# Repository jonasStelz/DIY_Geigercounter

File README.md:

# ESP32-S3 Geiger Counter PCB

A custom-designed **battery-powered** Geiger counter board created in **KiCad**, featuring an **ESP32-S3-WROOM-1** module, an LCD display, and a high-voltage section for driving a Geiger–Müller tube.

This project combines radiation detection with IoT capabilities, allowing live data display and wireless transmission without being tethered to a power source.

---

## Features

- **ESP32-S3-WROOM-1** microcontroller for high performance and Wi-Fi/Bluetooth connectivity  
- **LCD display** for real-time radiation readings and system status  
- Integrated **high-voltage generator** for Geiger–Müller tube operation  
- **USB-C** connector for charging and programming  
- **Battery-powered** for portable use (Li-ion/LiPo support)  
- Compact PCB layout for handheld or embedded use  
- Designed entirely in **KiCad**

---

## Hardware Overview

The PCB integrates both the high-voltage section (for the tube) and the low-voltage digital section (ESP32 + display + battery management) on the same board.  
Special care has been taken to separate HV signals from sensitive logic lines.

---

## Feedback & Contributions

This is my first PCB design combining high-voltage circuitry with an ESP32-S3 microcontroller.  
I welcome **design reviews, suggestions, and improvements** — especially regarding:  
- HV layout and safety clearances  
- EMC and noise reduction  
- Power supply stability (especially with battery use)  
- General PCB best practices  

If you spot an issue or have an idea, please open an **Issue** or submit a **Pull Request**.

---

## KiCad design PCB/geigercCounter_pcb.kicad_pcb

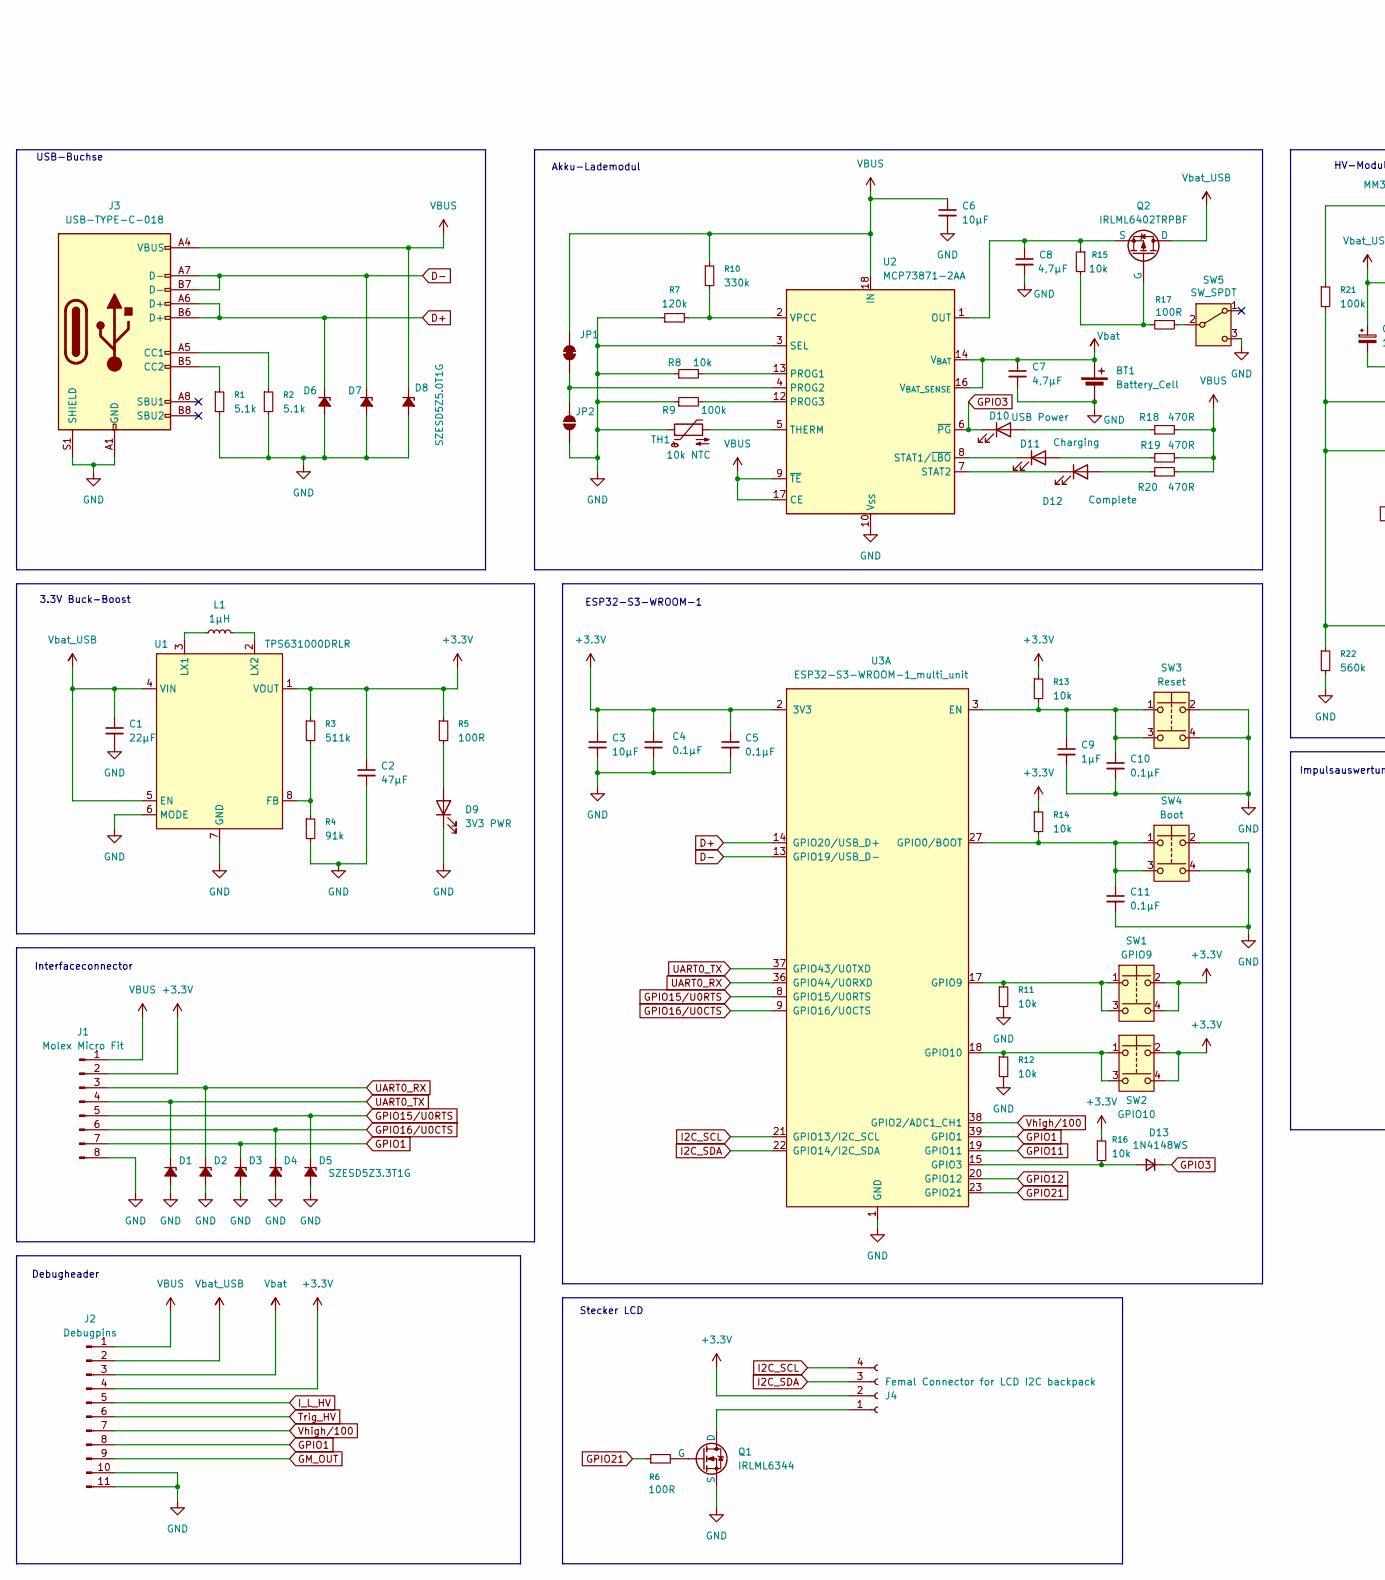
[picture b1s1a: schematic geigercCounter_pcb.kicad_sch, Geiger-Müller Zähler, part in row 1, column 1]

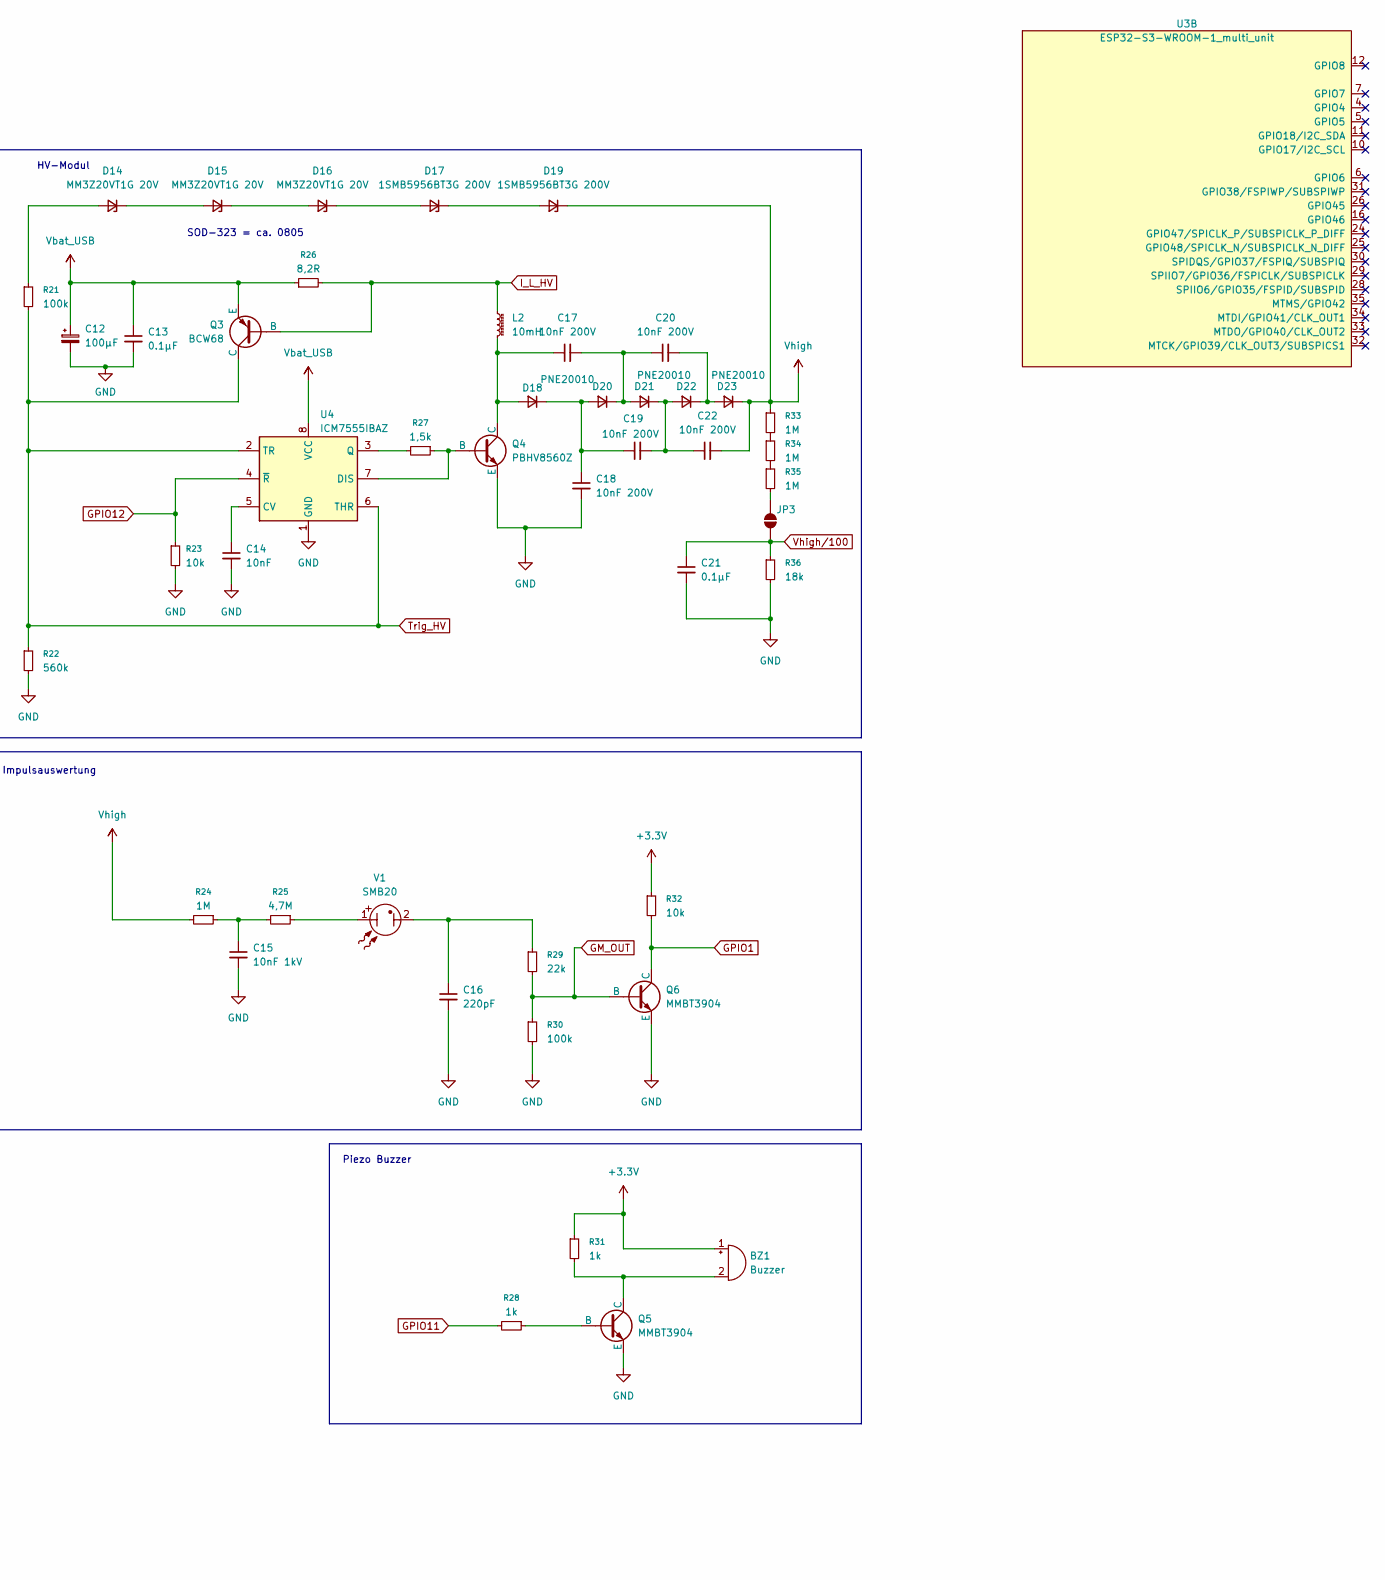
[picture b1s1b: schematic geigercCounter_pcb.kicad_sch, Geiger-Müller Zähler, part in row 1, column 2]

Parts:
BT1: Battery_Cell; JST_PH_B2B-PH-SM4-TB_1x02-1MP_P2.00mm_Vertical
BZ1: Buzzer; CMI-9705-0380
C1: 22µF; C_0805_2012Metric_Pad1.18x1.45mm_HandSolder
C2: 47µF; C_0805_2012Metric_Pad1.18x1.45mm_HandSolder
C3, C6: 10µF; C_0805_2012Metric_Pad1.18x1.45mm_HandSolder
C4, C5, C10, C11, C13, C21: 0.1µF; C_0805_2012Metric_Pad1.18x1.45mm_HandSolder
C7, C8: 4,7µF; C_0805_2012Metric_Pad1.18x1.45mm_HandSolder
C9: 1µF; C_0805_2012Metric_Pad1.18x1.45mm_HandSolder
C12: 100µF; CP_Elec_6.3x5.9
C14: 10nF; C_0805_2012Metric_Pad1.18x1.45mm_HandSolder
C15: 10nF 1kV; C_1206_3216Metric_Pad1.33x1.80mm_HandSolder
C16: 220pF; C_0805_2012Metric_Pad1.18x1.45mm_HandSolder
C17, C18, C19, C20, C22: 10nF 200V; C_0805_2012Metric_Pad1.18x1.45mm_HandSolder
D1, D2, D3, D4, D5: SZESD5Z3.3T1G; D_SOD-523
D6, D7, D8: SZESD5Z5.0T1G; D_SOD-523
D9: 3V3 PWR; LED_0805_2012Metric_Pad1.15x1.40mm_HandSolder
D10: USB Power; LED_0805_2012Metric_Pad1.15x1.40mm_HandSolder
D11: Charging; LED_0805_2012Metric_Pad1.15x1.40mm_HandSolder
D12: Complete; LED_0805_2012Metric_Pad1.15x1.40mm_HandSolder
D13: 1N4148WS; D_SOD-323_HandSoldering
D14, D15, D16: MM3Z20VT1G 20V; D_SOD-323_HandSoldering
D17, D19: 1SMB5956BT3G 200V; D_SMB_Handsoldering
D18, D20, D21, D22, D23: PNE20010; Nexperia_CFP3_SOD-123W
J1: Molex Micro Fit; Molex_Micro-Fit_3.0_43045-0810_2x04-1MP_P3.00mm_Horizontal
J2: Debugpins; PinHeader_1x11_P2.54mm_Vertical
J3: USB-TYPE-C-018; USB_C_Receptacle_GCT_USB4105-xx-A_16P_TopMnt_Horizontal
J4: Femal Connector for LCD I2C backpack; PinHeader_1x04_P2.54mm_Horizontal
JP1: SolderJumper_2_Bridged; SolderJumper-2_P1.3mm_Open_RoundedPad1.0x1.5mm
JP2, JP3: SolderJumper_2_Open; SolderJumper-2_P1.3mm_Open_RoundedPad1.0x1.5mm
L1: 1µH; Murata_DFE252012P
L2: 10mH; Inductor_wuerth_7447709222
Q1: IRLML6344; SOT-23-3
Q2: IRLML6402TRPBF; SOT-23-3
Q3: BCW68; SOT-23-3
Q4: PBHV8560Z; SOT-223-3_TabPin2
Q5, Q6: MMBT3904; SOT-23-3
R1, R2: 5.1k; R_0805_2012Metric_Pad1.20x1.40mm_HandSolder
R3: 511k; R_0805_2012Metric_Pad1.20x1.40mm_HandSolder
R4: 91k; R_0805_2012Metric_Pad1.20x1.40mm_HandSolder
R5, R6, R17: 100R; R_0805_2012Metric_Pad1.20x1.40mm_HandSolder
R7: 120k; R_0805_2012Metric_Pad1.20x1.40mm_HandSolder
R8, R11, R12, R13, R14, R15, R16, R23, R32: 10k; R_0805_2012Metric_Pad1.20x1.40mm_HandSolder
R9, R21, R30: 100k; R_0805_2012Metric_Pad1.20x1.40mm_HandSolder
R10: 330k; R_0805_2012Metric_Pad1.20x1.40mm_HandSolder
R18, R19, R20: 470R; R_0805_2012Metric_Pad1.20x1.40mm_HandSolder
R22: 560k; R_0805_2012Metric_Pad1.20x1.40mm_HandSolder
R24, R33, R34, R35: 1M; R_0805_2012Metric_Pad1.20x1.40mm_HandSolder
R25: 4,7M; R_0805_2012Metric_Pad1.20x1.40mm_HandSolder
R26: 8,2R; R_0805_2012Metric_Pad1.20x1.40mm_HandSolder
R27: 1,5k; R_0805_2012Metric_Pad1.20x1.40mm_HandSolder
R28, R31: 1k; R_0805_2012Metric_Pad1.20x1.40mm_HandSolder
R29: 22k; R_0805_2012Metric_Pad1.20x1.40mm_HandSolder
R36: 18k; R_0805_2012Metric_Pad1.20x1.40mm_HandSolder
SW1: GPIO9; SW_Push_1P1T_NO_E-Switch_TL3301NxxxxxG
SW2: GPIO10; SW_Push_1P1T_NO_E-Switch_TL3301NxxxxxG
SW3: Reset; SW_Push_1P1T_NO_E-Switch_TL3301NxxxxxG
SW4: Boot; SW_Push_1P1T_NO_E-Switch_TL3301NxxxxxG
SW5: SW_SPDT; SW_SPDT_PCM12
TH1: 10k NTC; R_0805_2012Metric_Pad1.20x1.40mm_HandSolder
U1: TPS631000DRLR; SOT-583-8
U2: MCP73871-2AA; QFN-20-1EP_4x4mm_P0.5mm_EP2.5x2.5mm
U3: ESP32-S3-WROOM-1_multi_unit; ESP32-S3-WROOM-1
U4: ICM7555IBAZ; SOIC-8_3.9x4.9mm_P1.27mm
V1: SMB20; SBM-20

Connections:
+3.3V: BZ1.1 (+), C2.1, C3.1, C4.1, C5.1, J1.2, J2.4, J4.2, R3.1, R5.1, R13.1, R14.1, R16.1, R31.1, R32.1, SW1.2, SW1.4 (1), SW2.2, SW2.4 (2), U1.1 (VOUT), U3.2 (3V3)
D+: D6.1 (K), J3.A6 (D+), J3.B6 (D+), U3.14 (GPIO20/USB_D+)
D-: D7.1 (K), J3.A7 (D-), J3.B7 (D-), U3.13 (GPIO19/USB_D-)
GM_OUT: J2.9, Q6.1 (B), R29.2, R30.1
GND: BT1.2 (-), C1.2, C2.2, C3.2, C4.2, C5.2, C6.2, C7.2, C8.2, C9.2, C10.2, C11.2, C12.2, C13.2, C14.2, C15.2, C16.2, C18.2, C21.2, D1.2 (A), D2.2 (A), D3.2 (A), D4.2 (A), D5.2 (A), D6.2 (A), D7.2 (A), D8.2 (A), D9.1 (K), J1.8, J1.MP, J2.10, J2.11, J3.A1 (GND), J3.A12 (GND), J3.B1 (GND), J3.B12 (GND), J3.S1 (SHIELD), JP2.1 (A), Q1.2 (S), Q4.3 (E), Q5.2 (E), Q6.2 (E), R1.2, R2.2, R4.2, R7.1, R8.1, R9.1, R11.2, R12.2, R22.2, R23.2, R30.2, R36.2, SW3.2, SW3.4 (2), SW4.2, SW4.4 (1), SW5.3 (C), TH1.1, U1.6 (MODE), U1.7 (GND), U2.3 (SEL), U2.10 (V_{SS}), U2.11 (V_{SS}), U2.21 (V_{SS}), U3.1 (GND), U3.40 (GND), U3.41 (GND), U4.1 (GND)
GPIO1: D3.1 (K), J1.7, J2.8, Q6.3 (C), R32.2, U3.39 (GPIO1)
GPIO3: D10.1 (K), D13.1 (K), U2.6 (~PG)
GPIO11: R28.2, U3.19 (GPIO11)
GPIO12: R23.1, U3.20 (GPIO12), U4.4 (~R)
GPIO15/U0RTS: D5.1 (K), J1.5, U3.8 (GPIO15/U0RTS)
GPIO16/U0CTS: D4.1 (K), J1.6, U3.9 (GPIO16/U0CTS)
GPIO21: R6.1, U3.23 (GPIO21)
I2C_SCL: J4.4, U3.21 (GPIO13/I2C_SCL)
I2C_SDA: J4.3, U3.22 (GPIO14/I2C_SDA)
I_L_HV: J2.5, L2.1, Q3.1 (B), R26.2
unnamed: BZ1.2 (-), Q5.3 (C), R31.2
unnamed: C15.1, R24.1, R25.2
unnamed: C16.1, R29.1, V1.2
unnamed: D9.2 (A), R5.2
unnamed: D10.2 (A), R18.1
unnamed: D11.2 (A), R19.2
unnamed: D11.1 (K), U2.8 (STAT1/~LBO)
unnamed: D12.2 (A), R20.1
unnamed: D12.1 (K), U2.7 (STAT2)
unnamed: D13.2 (A), R16.2, U3.15 (GPIO3)
unnamed: D14.2 (A), R21.1
unnamed: D14.1 (K), D15.2 (A)
unnamed: D15.1 (K), D16.2 (A)
unnamed: D16.1 (K), D17.2 (A)
unnamed: D17.1 (K), D19.2 (A)
unnamed: C17.1, D18.2 (A), L2.2, Q4.2 (C)
unnamed: C18.1, C19.1, D18.1 (K), D20.2 (A)
unnamed: C17.2, C20.1, D20.1 (K), D21.2 (A)
unnamed: C19.2, C22.1, D21.1 (K), D22.2 (A)
unnamed: C20.2, D22.1 (K), D23.2 (A)
unnamed: J3.A5 (CC1), R2.1
unnamed: J3.B5 (CC2), R1.1
unnamed: J4.1, Q1.3 (D)
unnamed: JP1.1 (A), JP2.2 (B), U2.4 (PROG2)
unnamed: JP3.2 (B), R35.2
unnamed: Q1.1 (G), R6.2
unnamed: Q2.1 (G), R15.2, R17.2
unnamed: C8.1, Q2.2 (S), R15.1, U2.1 (OUT), U2.20 (OUT)
unnamed: Q4.1 (B), R27.1, U4.7 (DIS)
unnamed: Q5.1 (B), R28.1
unnamed: R25.1, V1.1
unnamed: R33.2, R34.1
unnamed: R34.2, R35.1
unnamed: R17.1, SW5.2 (B)
unnamed: R3.2, R4.1, U1.8 (FB)
unnamed: L1.1, U1.3 (LX1)
unnamed: L1.2, U1.2 (LX2)
unnamed: R8.2, U2.13 (PROG1)
unnamed: R9.2, U2.12 (PROG3)
unnamed: TH1.2, U2.5 (THERM)
unnamed: R7.2, R10.2, U2.2 (VPCC)
unnamed: C9.1, C10.1, R13.2, SW3.1, SW3.3 (1), U3.3 (EN)
unnamed: C11.1, R14.2, SW4.1, SW4.3 (1), U3.27 (GPIO0/BOOT)
unnamed: R11.1, SW1.1, SW1.3 (1), U3.17 (GPIO9)
unnamed: R12.1, SW2.1, SW2.3 (1), U3.18 (GPIO10)
unnamed: C14.1, U4.5 (CV)
unnamed: R27.2, U4.3 (Q)
Trig_HV: J2.6, Q3.3 (C), R21.2, R22.1, U4.2 (TR), U4.6 (THR)
UART0_RX: D2.1 (K), J1.3, U3.36 (GPIO44/U0RXD)
UART0_TX: D1.1 (K), J1.4, U3.37 (GPIO43/U0TXD)
VBUS: C6.1, D8.1 (K), J1.1, J2.1, J3.A4 (VBUS), J3.A9 (VBUS), J3.B4 (VBUS), J3.B9 (VBUS), JP1.2 (B), R10.1, R18.2, R19.1, R20.2, U2.9 (~TE), U2.17 (CE), U2.18 (IN), U2.19 (IN)
Vbat: BT1.1 (+), C7.1, J2.3, U2.14 (V_{BAT}), U2.15 (V_{BAT}), U2.16 (V_{BAT_SENSE})
Vbat_USB: C1.1, C12.1, C13.1, J2.2, Q2.3 (D), Q3.2 (E), R26.1, U1.4 (VIN), U1.5 (EN), U4.8 (VCC)
Vhigh: C22.2, D19.1 (K), D23.1 (K), R24.2, R33.1
Vhigh/100: C21.1, J2.7, JP3.1 (A), R36.1, U3.38 (GPIO2/ADC1_CH1)

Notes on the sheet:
3.3V Buck-Boost
Stecker LCD
USB-Buchse
Akku-Lademodul
ESP32-S3-WROOM-1
Impulsauswertung
SOD-323 = ca. 0805
HV-Modul
Interfaceconnector
Piezo Buzzer
Debugheader

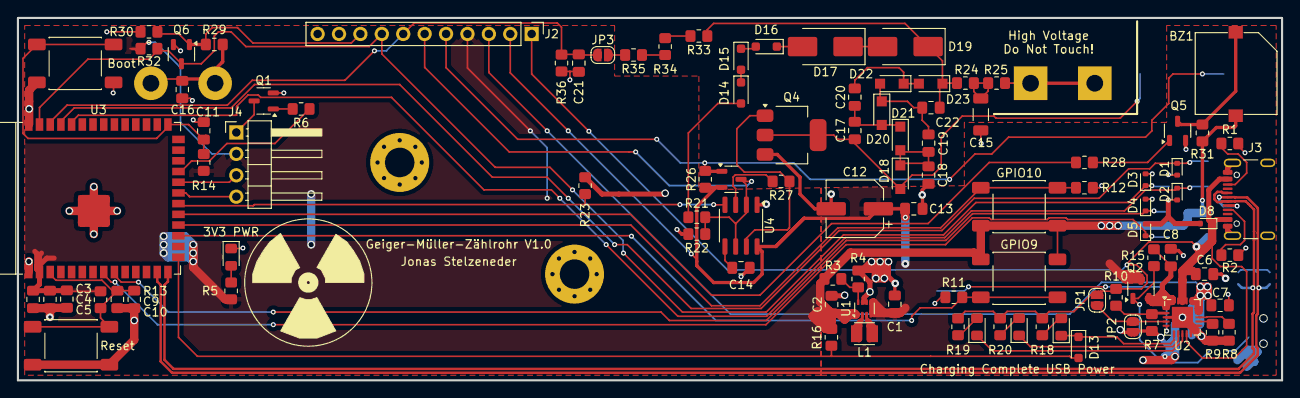
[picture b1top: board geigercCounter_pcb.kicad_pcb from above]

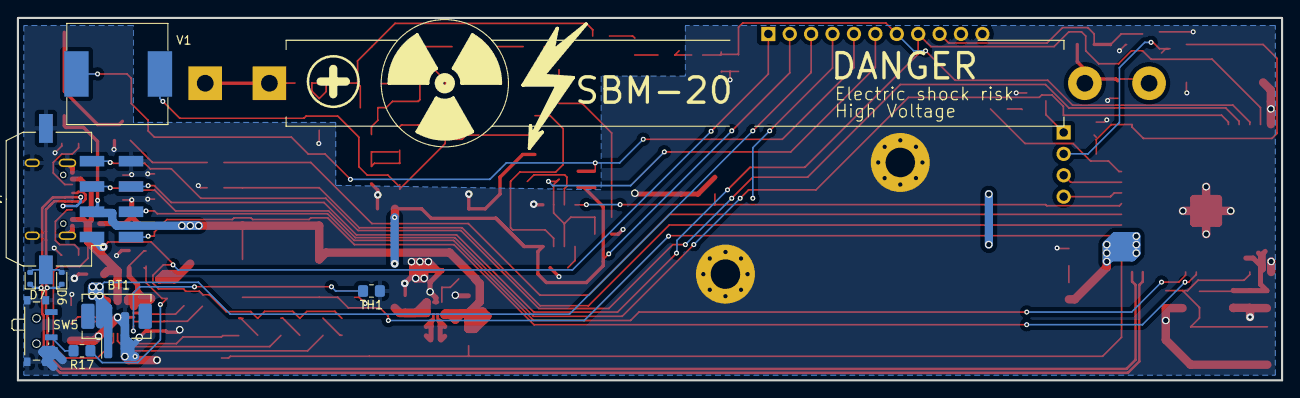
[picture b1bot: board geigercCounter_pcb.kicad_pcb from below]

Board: 2 copper layers, 150.0 x 43.0 mm, 109 parts (9 on the bottom side), 70 nets.

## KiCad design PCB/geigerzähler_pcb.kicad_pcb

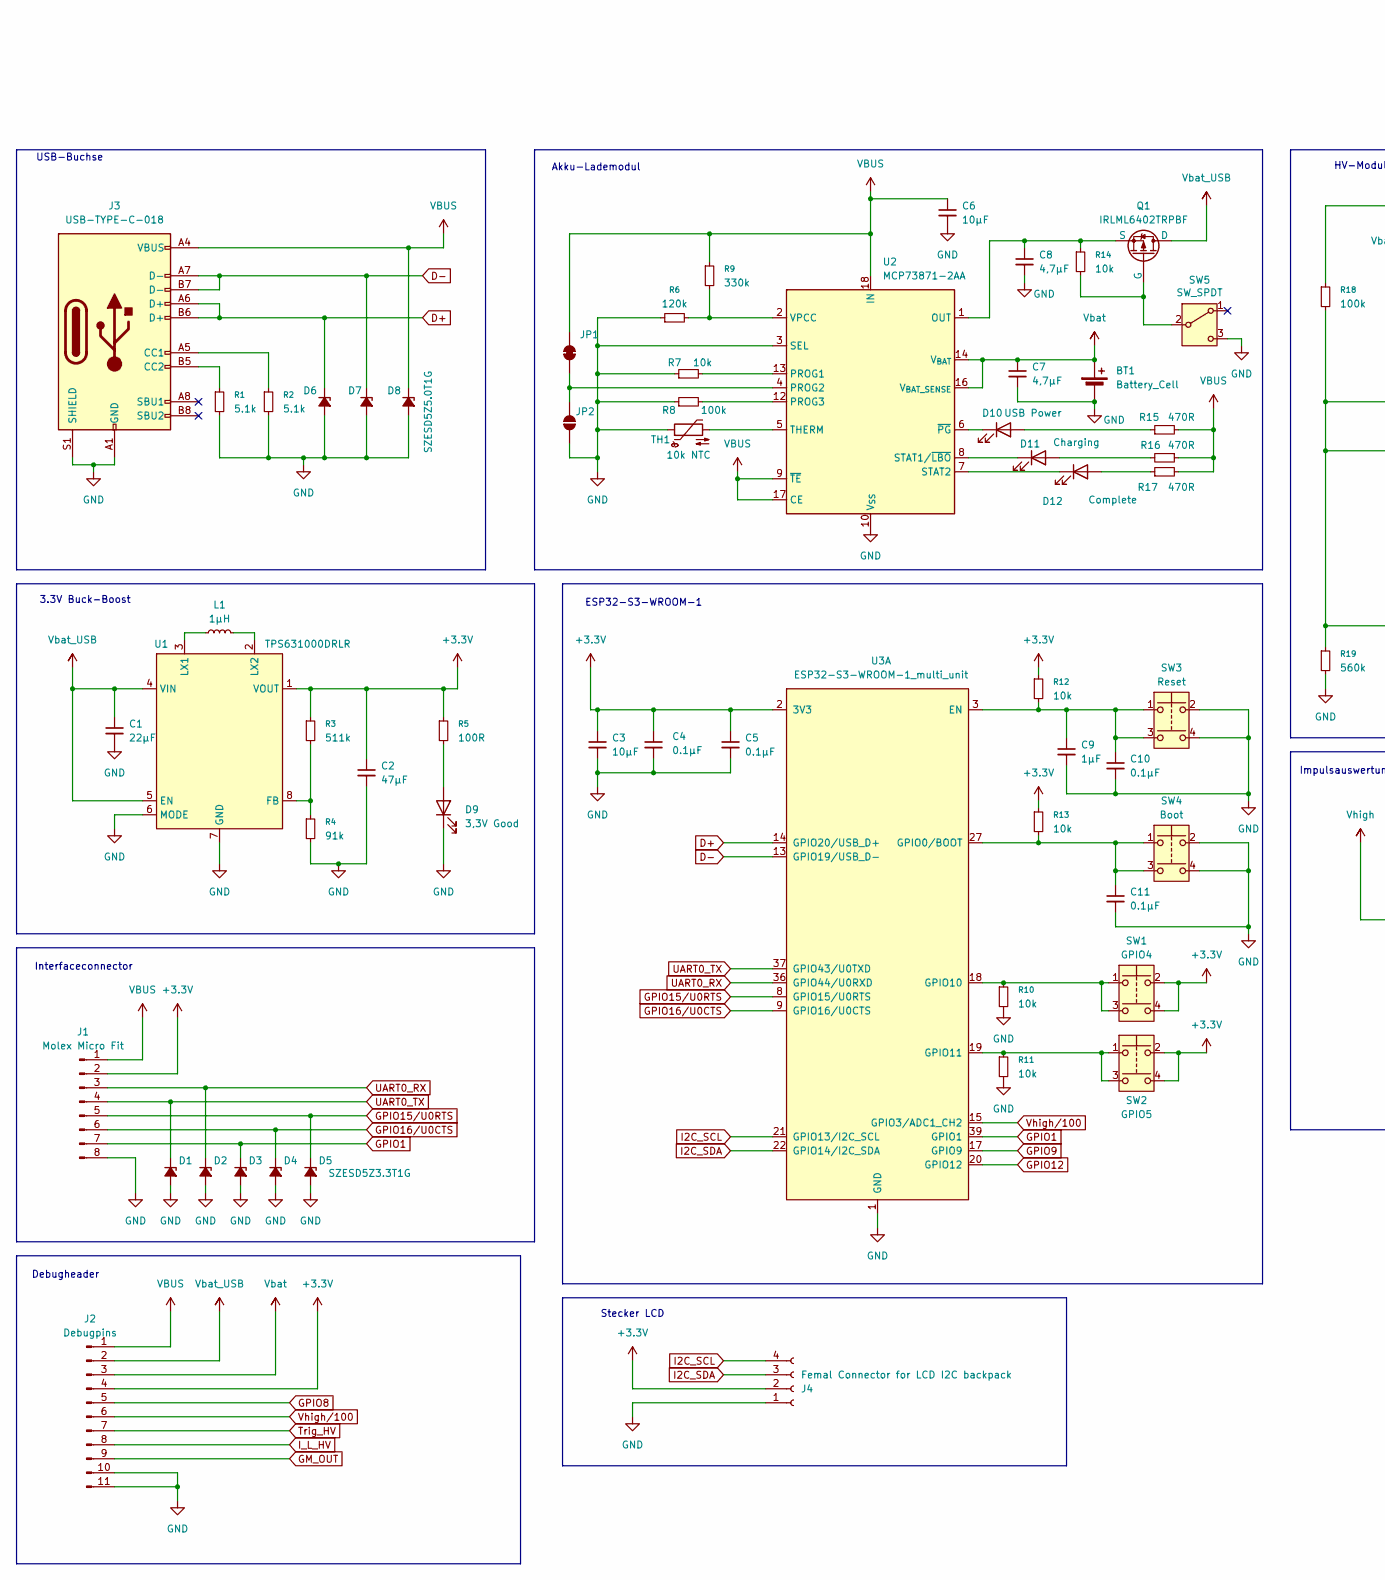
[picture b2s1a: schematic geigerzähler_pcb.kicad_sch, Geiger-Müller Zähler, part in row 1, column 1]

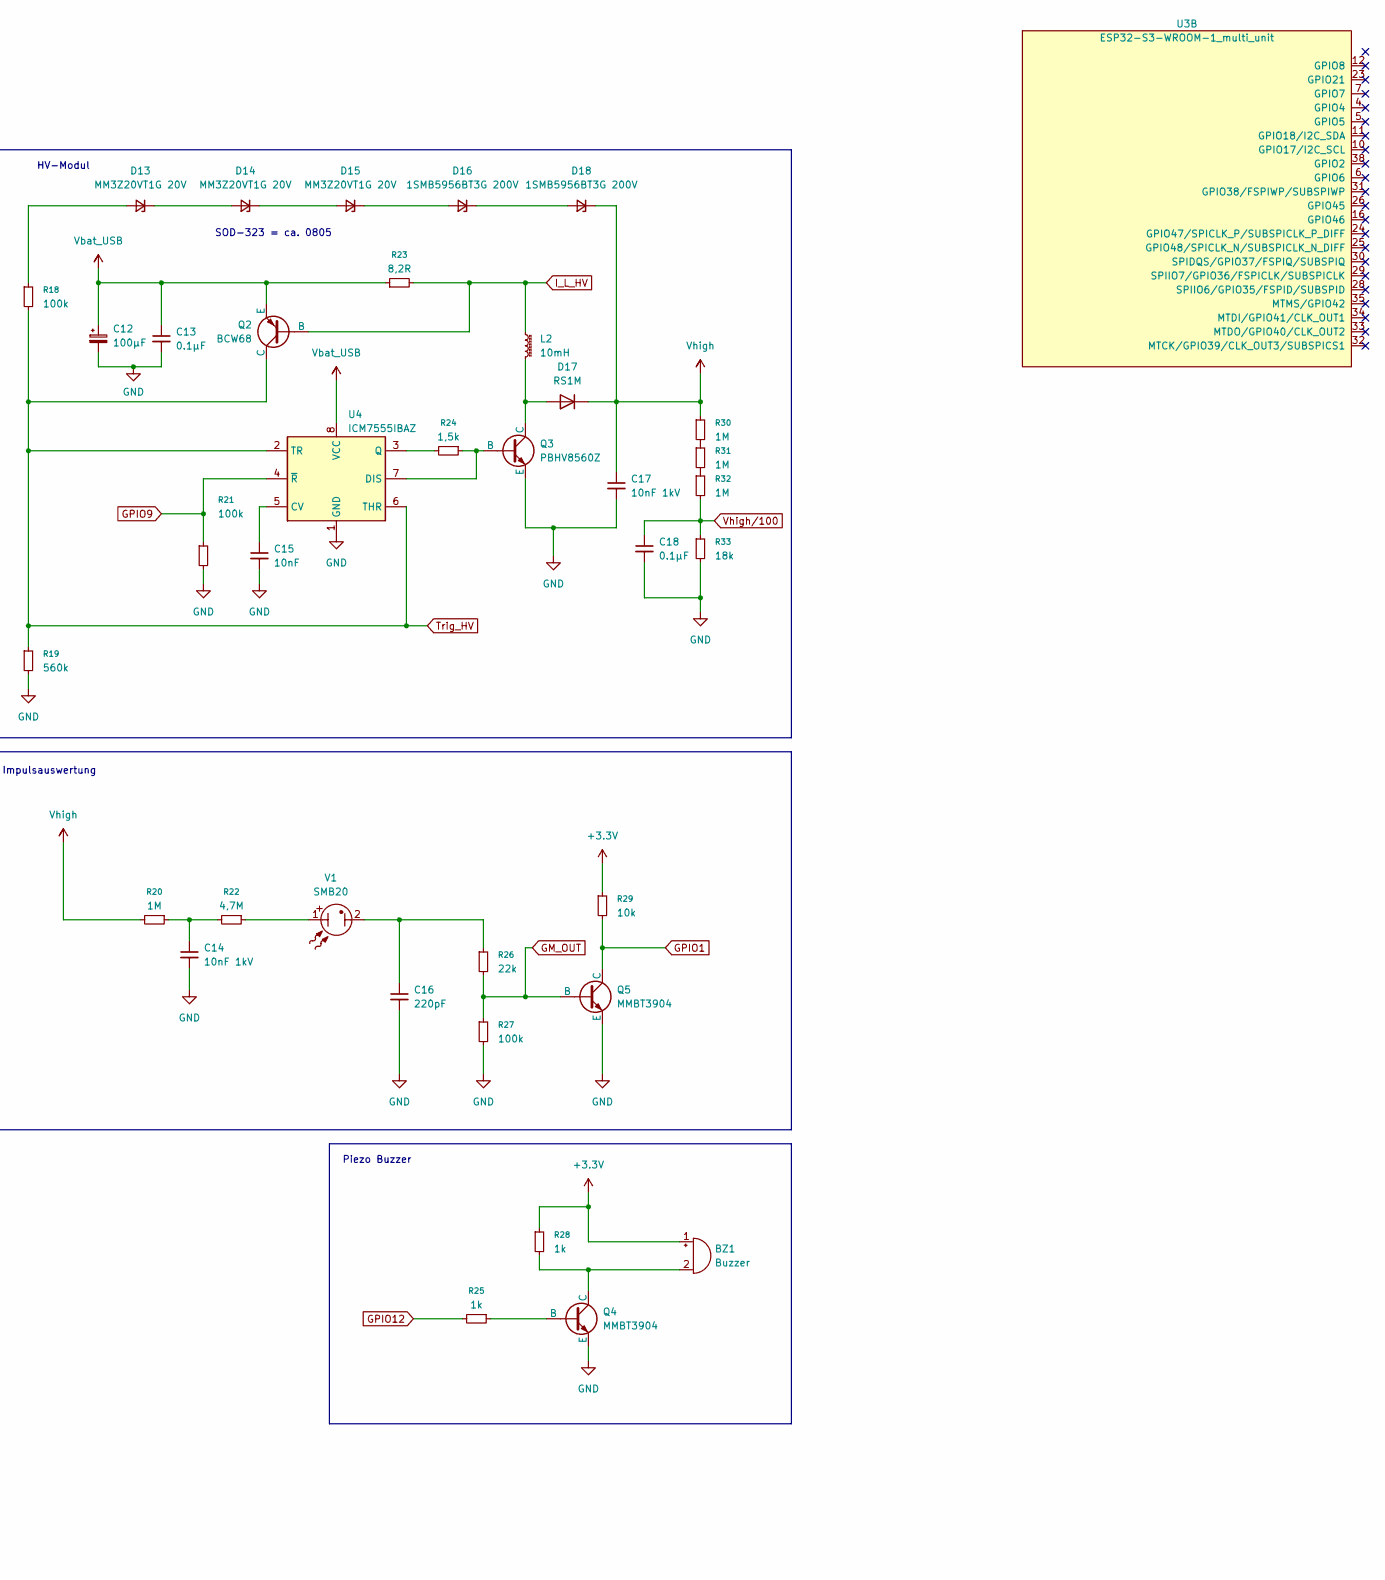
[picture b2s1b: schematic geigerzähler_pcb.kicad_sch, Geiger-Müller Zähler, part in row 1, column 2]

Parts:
BT1: Battery_Cell; JST_PH_B2B-PH-SM4-TB_1x02-1MP_P2.00mm_Vertical
BZ1: Buzzer; CMI-9705-0380
C1: 22µF; C_0805_2012Metric_Pad1.18x1.45mm_HandSolder
C2: 47µF; C_0805_2012Metric_Pad1.18x1.45mm_HandSolder
C3, C6: 10µF; C_0805_2012Metric_Pad1.18x1.45mm_HandSolder
C4, C5, C10, C11, C13, C18: 0.1µF; C_0805_2012Metric_Pad1.18x1.45mm_HandSolder
C7, C8: 4,7µF; C_0805_2012Metric_Pad1.18x1.45mm_HandSolder
C9: 1µF; C_0805_2012Metric_Pad1.18x1.45mm_HandSolder
C12: 100µF; CP_Elec_6.3x5.9
C14, C17: 10nF 1kV; C_1206_3216Metric_Pad1.33x1.80mm_HandSolder
C15: 10nF; C_0805_2012Metric_Pad1.18x1.45mm_HandSolder
C16: 220pF; C_0805_2012Metric_Pad1.18x1.45mm_HandSolder
D1, D2, D3, D4, D5: SZESD5Z3.3T1G; D_SOD-523
D6, D7, D8: SZESD5Z5.0T1G; D_SOD-523
D9: 3,3V Good; LED_0805_2012Metric_Pad1.15x1.40mm_HandSolder
D10: USB Power; LED_0805_2012Metric_Pad1.15x1.40mm_HandSolder
D11: Charging; LED_0805_2012Metric_Pad1.15x1.40mm_HandSolder
D12: Complete; LED_0805_2012Metric_Pad1.15x1.40mm_HandSolder
D13, D14, D15: MM3Z20VT1G 20V; D_SOD-323_HandSoldering
D16, D18: 1SMB5956BT3G 200V; D_SMB_Handsoldering
D17: RS1M; D_SMA
J1: Molex Micro Fit; Molex_Micro-Fit_3.0_43045-0810_2x04-1MP_P3.00mm_Horizontal
J2: Debugpins; PinHeader_1x11_P2.54mm_Vertical
J3: USB-TYPE-C-018; USB_C_Receptacle_GCT_USB4105-xx-A_16P_TopMnt_Horizontal
J4: Femal Connector for LCD I2C backpack; PinHeader_1x04_P2.54mm_Horizontal
JP1: SolderJumper_2_Bridged; SolderJumper-2_P1.3mm_Open_RoundedPad1.0x1.5mm
JP2: SolderJumper_2_Open; SolderJumper-2_P1.3mm_Open_RoundedPad1.0x1.5mm
L1: 1µH; Murata_DFE252012P
L2: 10mH; Inductor_wuerth_74404086103
Q1: IRLML6402TRPBF; SOT-23-3
Q2: BCW68; SOT-23-3
Q3: PBHV8560Z; SOT-223-3_TabPin2
Q4, Q5: MMBT3904; SOT-23-3
R1, R2: 5.1k; R_0805_2012Metric_Pad1.20x1.40mm_HandSolder
R3: 511k; R_0805_2012Metric_Pad1.20x1.40mm_HandSolder
R4: 91k; R_0805_2012Metric_Pad1.20x1.40mm_HandSolder
R5: 100R; R_0805_2012Metric_Pad1.20x1.40mm_HandSolder
R6: 120k; R_0805_2012Metric_Pad1.20x1.40mm_HandSolder
R7, R10, R11, R12, R13, R14, R29: 10k; R_0805_2012Metric_Pad1.20x1.40mm_HandSolder
R8, R18, R21, R27: 100k; R_0805_2012Metric_Pad1.20x1.40mm_HandSolder
R9: 330k; R_0805_2012Metric_Pad1.20x1.40mm_HandSolder
R15, R16, R17: 470R; R_0805_2012Metric_Pad1.20x1.40mm_HandSolder
R19: 560k; R_0805_2012Metric_Pad1.20x1.40mm_HandSolder
R20, R30, R31, R32: 1M; R_0805_2012Metric_Pad1.20x1.40mm_HandSolder
R22: 4,7M; R_0805_2012Metric_Pad1.20x1.40mm_HandSolder
R23: 8,2R; R_0805_2012Metric_Pad1.20x1.40mm_HandSolder
R24: 1,5k; R_0805_2012Metric_Pad1.20x1.40mm_HandSolder
R25, R28: 1k; R_0805_2012Metric_Pad1.20x1.40mm_HandSolder
R26: 22k; R_0805_2012Metric_Pad1.20x1.40mm_HandSolder
R33: 18k; R_0805_2012Metric_Pad1.20x1.40mm_HandSolder
SW1: GPIO4; SW_Push_1P1T_NO_E-Switch_TL3301NxxxxxG
SW2: GPIO5; SW_Push_1P1T_NO_E-Switch_TL3301NxxxxxG
SW3: Reset; SW_Push_1P1T_NO_E-Switch_TL3301NxxxxxG
SW4: Boot; SW_Push_1P1T_NO_E-Switch_TL3301NxxxxxG
SW5: SW_SPDT; SW_SPDT_PCM12
TH1: 10k NTC; R_0805_2012Metric_Pad1.20x1.40mm_HandSolder
U1: TPS631000DRLR; SOT-583-8
U2: MCP73871-2AA; QFN-20-1EP_4x4mm_P0.5mm_EP2.5x2.5mm
U3: ESP32-S3-WROOM-1_multi_unit; ESP32-S3-WROOM-1
U4: ICM7555IBAZ; SOIC-8_3.9x4.9mm_P1.27mm
V1: SMB20; SBM-20

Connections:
+3.3V: BZ1.1 (+), C2.1, C3.1, C4.1, C5.1, J1.2, J2.4, J4.2, R3.1, R5.1, R12.1, R13.1, R28.1, R29.1, SW1.2, SW1.4 (1), SW2.2, SW2.4 (2), U1.1 (VOUT), U3.2 (3V3)
D+: D6.1 (K), J3.A6 (D+), J3.B6 (D+), U3.14 (GPIO20/USB_D+)
D-: D7.1 (K), J3.A7 (D-), J3.B7 (D-), U3.13 (GPIO19/USB_D-)
GM_OUT: J2.9, Q5.1 (B), R26.2, R27.1
GPIO1: D3.1 (K), J1.7, Q5.3 (C), R29.2, U3.39 (GPIO1)
GPIO8: J2.5
GPIO9: R21.1, U3.17 (GPIO9), U4.4 (~R)
GPIO12: R25.2, U3.20 (GPIO12)
GPIO15/U0RTS: D5.1 (K), J1.5, U3.8 (GPIO15/U0RTS)
GPIO16/U0CTS: D4.1 (K), J1.6, U3.9 (GPIO16/U0CTS)
I2C_SCL: J4.4, U3.21 (GPIO13/I2C_SCL)
I2C_SDA: J4.3, U3.22 (GPIO14/I2C_SDA)
I_L_HV: J2.8, L2.1, Q2.1 (B), R23.2
unnamed: BZ1.2 (-), Q4.3 (C), R28.2
unnamed: C14.1, R20.1, R22.2
unnamed: C16.1, R26.1, V1.2
unnamed: D9.2 (A), R5.2
unnamed: D10.2 (A), R15.1
unnamed: D10.1 (K), U2.6 (~PG)
unnamed: D11.2 (A), R16.2
unnamed: D11.1 (K), U2.8 (STAT1/~LBO)
unnamed: D12.2 (A), R17.1
unnamed: D12.1 (K), U2.7 (STAT2)
unnamed: D13.2 (A), R18.1
unnamed: D13.1 (K), D14.2 (A)
unnamed: D14.1 (K), D15.2 (A)
unnamed: D15.1 (K), D16.2 (A)
unnamed: D16.1 (K), D18.2 (A)
unnamed: D17.2 (A), L2.2, Q3.2 (C)
unnamed: J3.A5 (CC1), R2.1
unnamed: J3.B5 (CC2), R1.1
unnamed: JP1.1 (A), JP2.2 (B), U2.4 (PROG2)
unnamed: Q1.2 (G), R14.2, SW5.2 (B)
unnamed: C8.1, Q1.3 (S), R14.1, U2.1 (OUT), U2.20 (OUT)
unnamed: Q3.1 (B), R24.1, U4.7 (DIS)
unnamed: Q4.1 (B), R25.1
unnamed: R22.1, V1.1
unnamed: R30.2, R31.1
unnamed: R31.2, R32.1
unnamed: R3.2, R4.1, U1.8 (FB)
unnamed: L1.1, U1.3 (LX1)
unnamed: L1.2, U1.2 (LX2)
unnamed: R7.2, U2.13 (PROG1)
unnamed: R8.2, U2.12 (PROG3)
unnamed: TH1.2, U2.5 (THERM)
unnamed: R6.2, R9.2, U2.2 (VPCC)
unnamed: C9.1, C10.1, R12.2, SW3.1, SW3.3 (1), U3.3 (EN)
unnamed: C11.1, R13.2, SW4.1, SW4.3 (1), U3.27 (GPIO0/BOOT)
unnamed: R10.1, SW1.1, SW1.3 (1), U3.18 (GPIO10)
unnamed: R11.1, SW2.1, SW2.3 (1), U3.19 (GPIO11)
unnamed: C15.1, U4.5 (CV)
unnamed: R24.2, U4.3 (Q)
Trig_HV: J2.7, Q2.3 (C), R18.2, R19.1, U4.2 (TR), U4.6 (THR)
UART0_RX: D2.1 (K), J1.3, U3.36 (GPIO44/U0RXD)
UART0_TX: D1.1 (K), J1.4, U3.37 (GPIO43/U0TXD)
Vbat: BT1.1 (+), C7.1, J2.3, U2.14 (V_{BAT}), U2.15 (V_{BAT}), U2.16 (V_{BAT_SENSE})
Vbat_USB: C1.1, C12.1, C13.1, J2.2, Q1.1 (D), Q2.2 (E), R23.1, U1.4 (VIN), U1.5 (EN), U4.8 (VCC)
Vhigh: C17.1, D17.1 (K), D18.1 (K), R20.2, R30.1

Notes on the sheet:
3.3V Buck-Boost
Stecker LCD
USB-Buchse
Akku-Lademodul
ESP32-S3-WROOM-1
Impulsauswertung
SOD-323 = ca. 0805
HV-Modul
Interfaceconnector
Piezo Buzzer
Debugheader

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
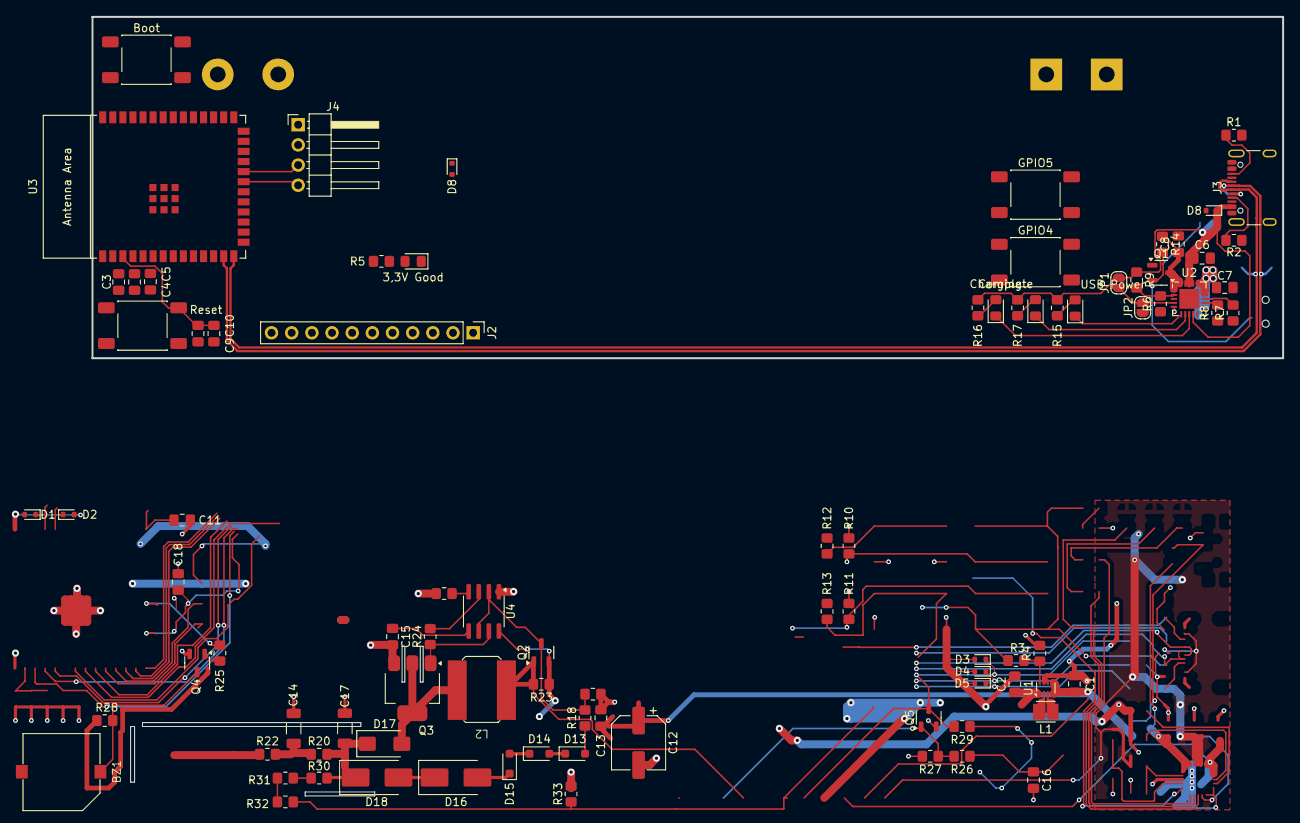
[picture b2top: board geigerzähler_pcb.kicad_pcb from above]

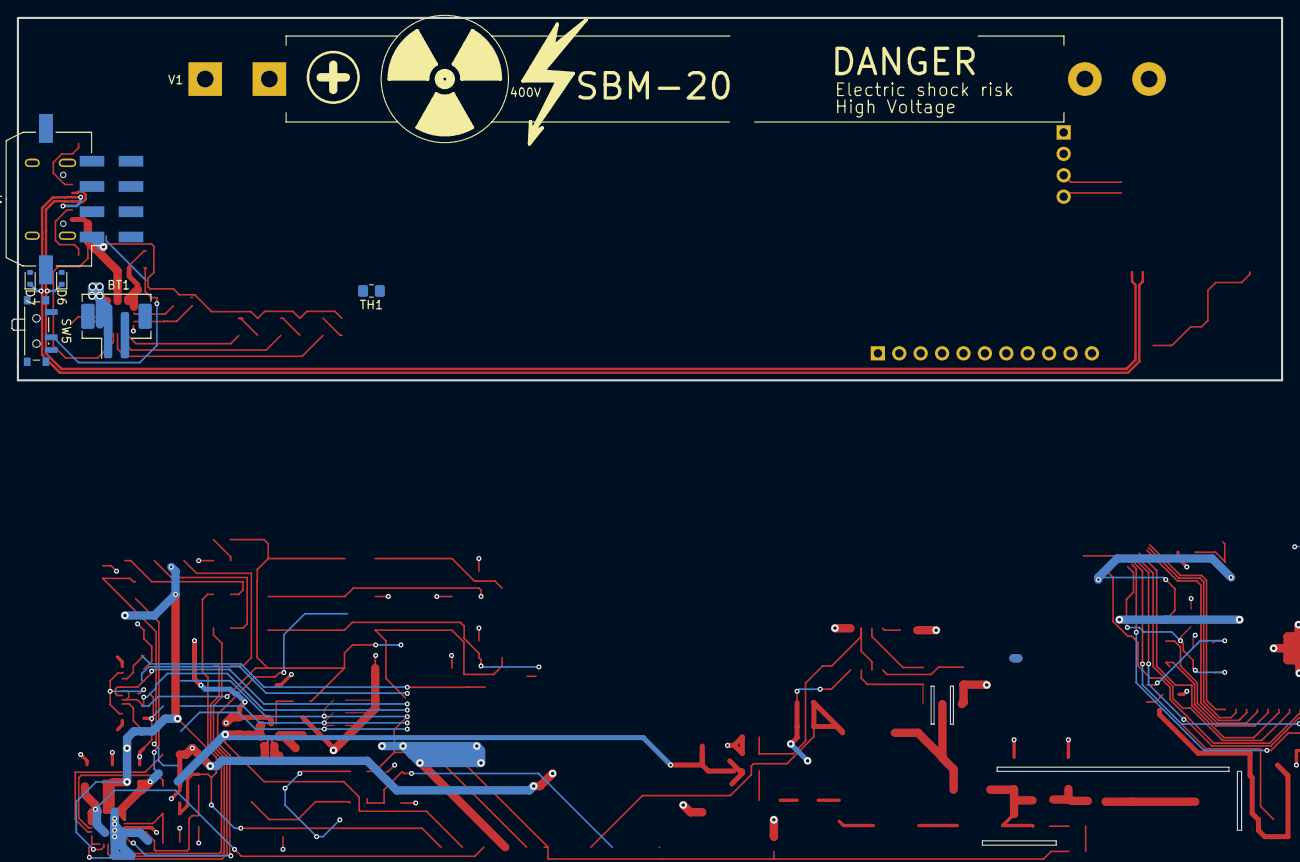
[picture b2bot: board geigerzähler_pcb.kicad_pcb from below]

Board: 2 copper layers, 150.0 x 98.0 mm, 96 parts (7 on the bottom side), 60 nets.

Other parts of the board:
D8#2: SZESD5Z5.0T1G; D_SOD-523

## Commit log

2025-08-08 08.08.2025_v0.2_start
2025-08-08 08.08.2025
2025-08-10 10.08.2025 Layout Version 0.2
2026-03-13 Bestellversion
2026-06-25 Software_InitialCommit
2026-06-25 Software_PulseCounter_geigerCore
2026-06-26 Buttons_LCD
2026-06-27 UI_Menu and general improvements
2026-06-29 Alarm_HVControl_Buzzer
